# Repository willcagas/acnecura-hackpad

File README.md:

# AcneCura Hackpad

AcneCura Hackpad is a macropad specifically designed for data annotation and labeling for types of acne and acne severities. It features six keys total, including six for annotating six different types of acne including whiteheads, blackheads, papules, pustules, nodules and cysts; two for undoing or redoing an annotation/label; and one key to start drawing a bounding box. A rotary encoder is used to rotate between five acne severities for multiclass classifcation labeling, inlcuding clear, almost clear, mild, moderate, and severe, all based on the IGA scale. An OLED is used to display whether data is being annotated for acne type or labelled for acne severity. The binded shortcuts are specifically designed for a Roboflow integration.

# Schematic and PCB

# CAD

# Components
- 9x Cherry MX Switches
- 9x Keycaps
- 1x EC11 Rotary Encoder
- 1x 0.91" OLED Display
- 1x XIAO RP2040
- Custom 3D Printed Top Case
- Custom 3D Printed Bottom Case

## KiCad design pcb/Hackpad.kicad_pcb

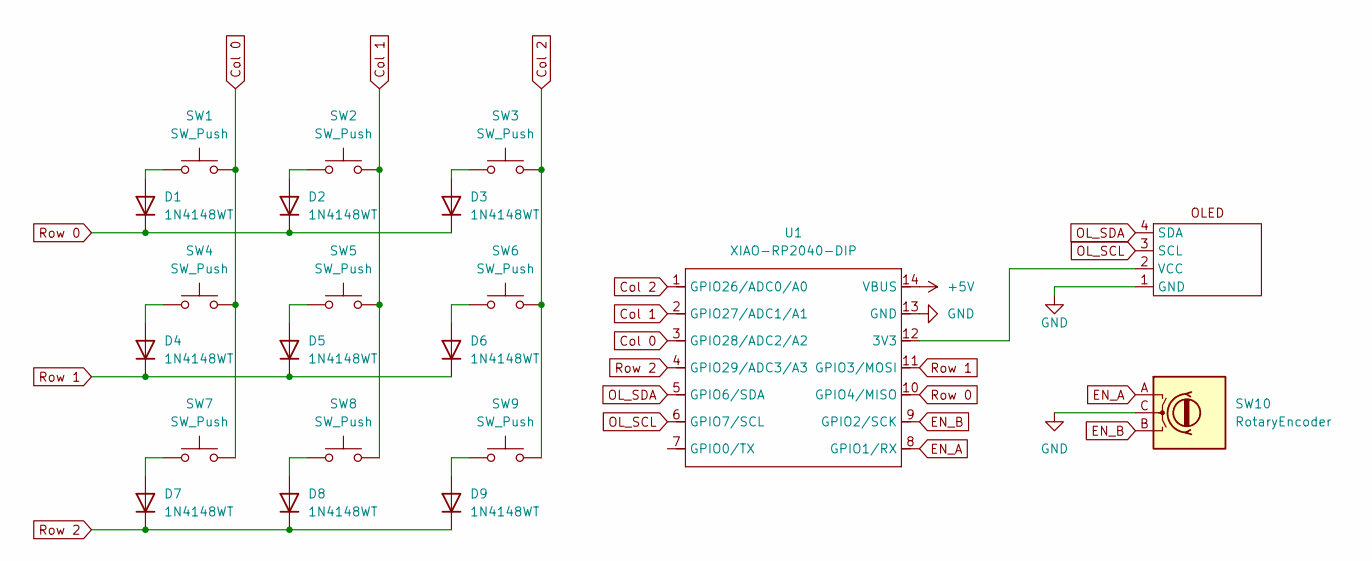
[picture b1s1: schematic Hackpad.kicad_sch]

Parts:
D1, D2, D3, D4, D5, D6, D7, D8, D9: 1N4148WT; D_DO-35_SOD27_P7.62mm_Horizontal
SW1, SW2, SW3, SW4, SW5, SW6, SW7, SW8, SW9: SW_Push; SW_Cherry_MX_1.00u_PCB
SW10: RotaryEncoder; RotaryEncoder_Alps_EC11E_Vertical_H20mm
U1: XIAO-RP2040-DIP
U2: SSD1306-0.91-OLED-4pin-128x32

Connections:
+5V: U1.14 (VBUS)
Col 0: SW1.2, SW4.2, SW7.2, U1.3 (GPIO28/ADC2/A2)
Col 1: SW2.2, SW5.2, SW8.2, U1.2 (GPIO27/ADC1/A1)
Col 2: SW3.2, SW6.2, SW9.2, U1.1 (GPIO26/ADC0/A0)
EN_A: SW10.A, U1.8 (GPIO1/RX)
EN_B: SW10.B, U1.9 (GPIO2/SCK)
GND: SW10.C, U1.13 (GND), U2.1 (GND)
unnamed: D1.2 (A), SW1.1
unnamed: D2.2 (A), SW2.1
unnamed: D3.2 (A), SW3.1
unnamed: D4.2 (A), SW4.1
unnamed: D5.2 (A), SW5.1
unnamed: D6.2 (A), SW6.1
unnamed: D7.2 (A), SW7.1
unnamed: D8.2 (A), SW8.1
unnamed: D9.2 (A), SW9.1
unnamed: U1.12 (3V3), U2.2 (VCC)
OL_SCL: U1.6 (GPIO7/SCL), U2.3 (SCL)
OL_SDA: U1.5 (GPIO6/SDA), U2.4 (SDA)
Row 0: D1.1 (K), D2.1 (K), D3.1 (K), U1.10 (GPIO4/MISO)
Row 1: D4.1 (K), D5.1 (K), D6.1 (K), U1.11 (GPIO3/MOSI)
Row 2: D7.1 (K), D8.1 (K), D9.1 (K), U1.4 (GPIO29/ADC3/A3)

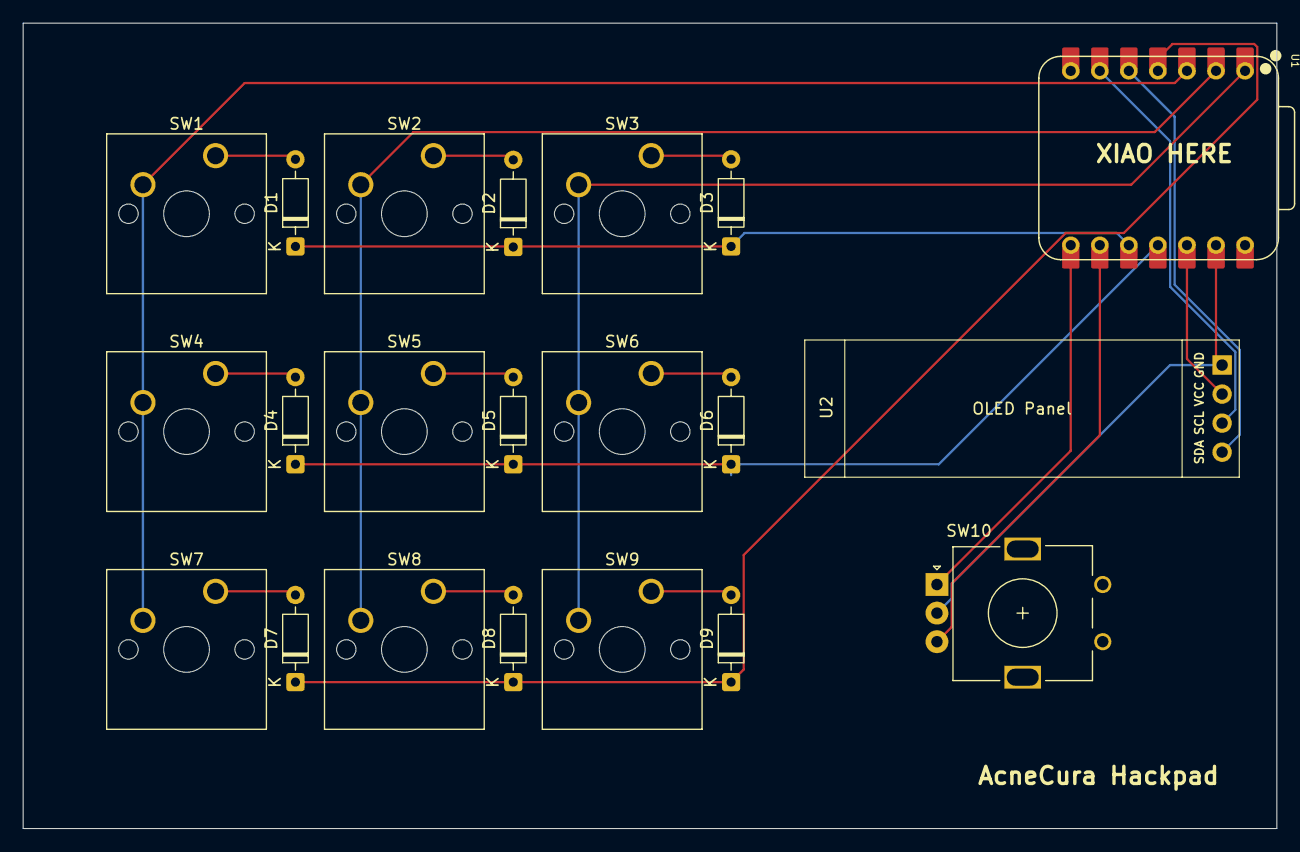
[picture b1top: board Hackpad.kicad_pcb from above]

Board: 2 copper layers, 109.6 x 70.4 mm, 21 parts (0 on the bottom side), 21 nets.

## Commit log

2025-07-02 inital commit
2025-07-02 add files
2025-07-02 minor cad edit
2025-07-02 add firmware code
2025-07-02 fix OLED schematic and pcb OLED wiring
2025-07-03 fix matrix wiring issue
2025-07-03 fixes
2025-07-04 add bom file
2025-07-04 cleanup gerber and drill files and add firmware to prod
